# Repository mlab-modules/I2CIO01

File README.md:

# I2CIO01A - I2C IO Expander

## Overview

The I2CIO01 module is a GPIO expander designed for operation in the range of 1.65 to 5.5 V. It provides general-purpose remote I/O expansion via the I²C interface. The module comprises two 8-bit Configurable, Input Ports, Output Port, and Polarity Inversion registers.

## Features

- **Operating Voltage:** 1.65 to 5.5 V
- **Interfaces:** I²C, up to 400 kHz
- **GPIO Ports:** 16-bit expansion using either TCA6416A or TCA9535 IC
- **Address Selection:**
  - TCA6416A: 2 I2C addresses, includes a reset pin
  - TCA9535: 4 I2C addresses
- **Interrupt Capabilities:** Both ICs support interrupt output
- **Package Dimensions:** 40.13 x 40.13 x 16 mm

## Technical Specifications

| Parameter        | Value        | Note                                |
|------------------|--------------|-------------------------------------|
| Power Supply     | Max. 3.6 V   |                                     |
| ICs Used         | TCA6416A or TCA9535 |                              |
| Interface bus        | I²C          | Frequency up to 400 kHz             |
| Main Usage       | I²C IO expander |                                     |
| Dimensions       | 40.13 x 40.13 x 16 mm | Height above the baseboard   |

## Design Details

### IC Selection variants
- **TCA6416A:**
  - Populate RES, do not populate ADR X
  - Jumper to Vccp and VDD
- **TCA9535:**
  - Do not populate RES, populate ADR X
  - Jumper to Vccp and VDD

### Schematic and Layout

The module's design and layout files can be found in the `hw/sch_pcb` directory. The board is designed using KiCad.

## Bill of Materials

| Designator      | Type                    | Package                    | Quantity |
|-----------------|-------------------------|----------------------------|----------|
| J3              | JUMP_3X2                | Pin_Header_Straight_2x03   | 1        |
| R1, R2, R3, ... | 10k                     | SMD-0805                   | 13       |
| U1              | TCA6416A                | TSSOP-28                   | 1        |
| J8, J5          | CONN1_2                 | Pin_Header_Straight_1x02   | 2        |
| P1, P2, P3, P4  | MountingHole_3mm        |                            | 4        |
| J1              | JUMP_2X2                | Pin_Header_Straight_2x02   | 1        |
| J2              | JUMP_5X2                | Pin_Header_Straight_2x05   | 1        |
| J6, J7          | JUMP_8X2                | Pin_Header_Straight_2x08   | 2        |
| J4, J9          | CONN_2                  | Pin_Header_Straight_1x02   | 2        |
| C1              | 10uF                    | SMD-0805                   | 1        |
| C2              | 100nF                   | SMD-0805                   | 1        |
| D1              | BZV55C-3,6V             | Diode-MiniMELF_Standard    | 1        |

## Assembly and Testing

1. **Assembly:** Follow the provided schematic and BOM for assembling the module.
2. **Initial Inspection:** Perform a visual inspection to ensure no shorts on the power supply.
3. **Testing:** No additional setup is required beyond the initial inspection.

For more detailed information on each component, please refer to their respective datasheets:

- [TCA6416A Datasheet](https://www.ti.com/product/TCA6416A)
- [TCA9535 Datasheet](https://www.ti.com/product/TCA9535)

## Contributing

Contributions are welcome! Please fork this repository and submit a pull request with your changes.

## Contact

For more information, visit the [MLAB website](http://www.mlab.cz) or contact us at support@mlab.cz.

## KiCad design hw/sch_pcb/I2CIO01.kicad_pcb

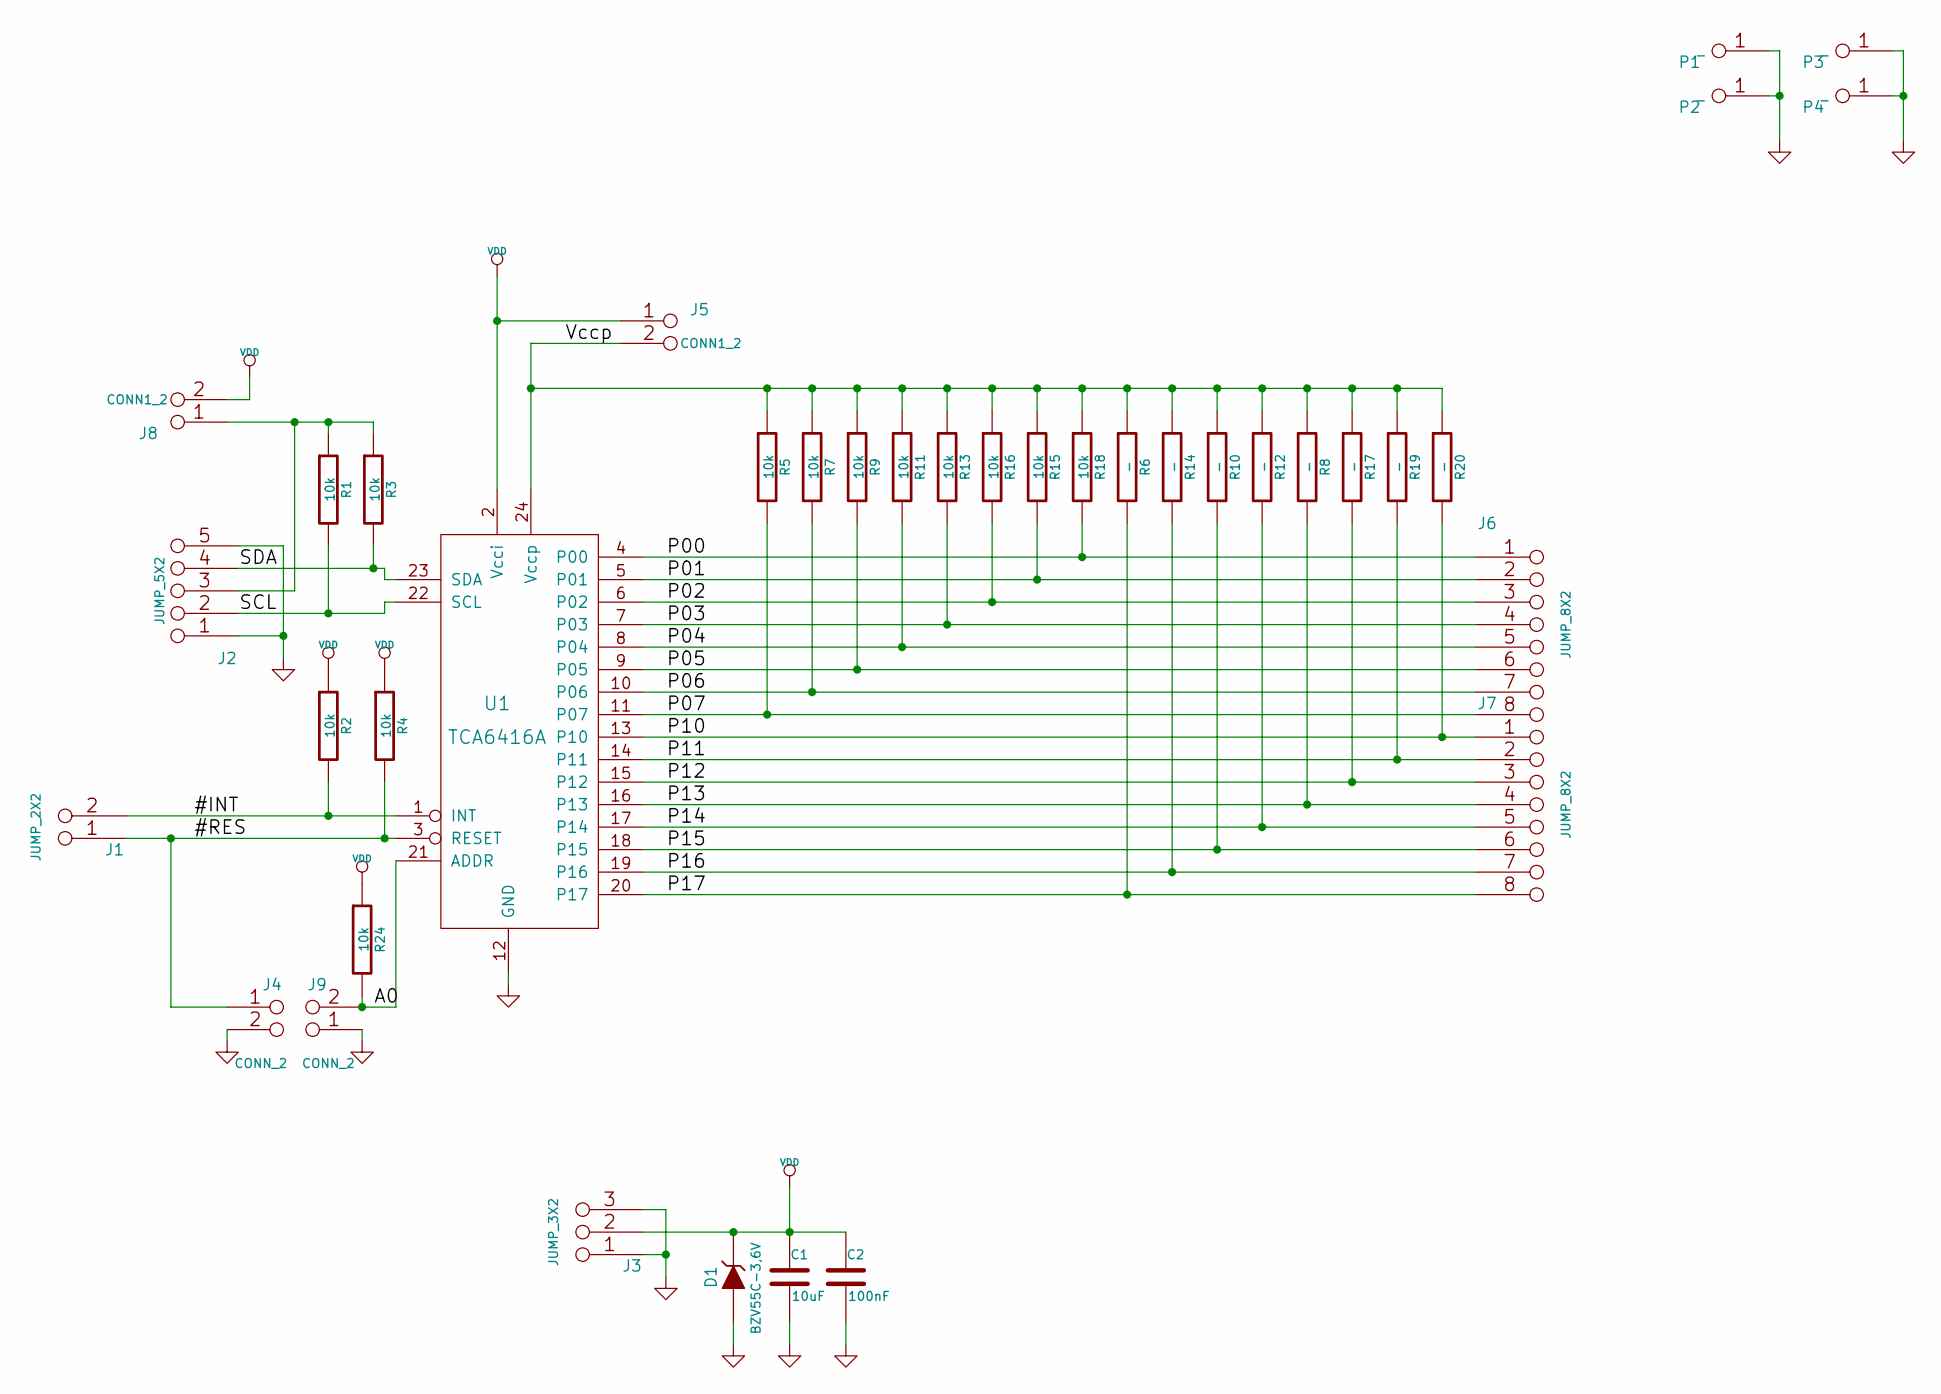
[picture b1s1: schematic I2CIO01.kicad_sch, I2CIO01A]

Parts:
C1: 10uF; SMD-0805
C2: 100nF; SMD-0805
D1: BZV55C-3,6V; Diode-MiniMELF_Standard
J1: JUMP_2X2; Pin_Header_Straight_2x02
J2: JUMP_5X2; Pin_Header_Straight_2x05
J3: JUMP_3X2; Pin_Header_Straight_2x03
J4, J9: CONN_2; Pin_Header_Straight_1x02
J5, J8: CONN1_2; Pin_Header_Straight_1x02
J6, J7: JUMP_8X2; Pin_Header_Straight_2x08
P1, P2, P3, P4: _; MountingHole_3mm
R1, R2, R3, R4, R5, R7, R9, R11, R13, R15, R16, R18, R24: 10k; SMD-0805
R6, R8, R10, R12, R14, R17, R19, R20: -; SMD-0805
U1: TCA6416A; TSSOP-28

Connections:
/#INT: J1.2 (1), J1.3, R2.2, U1.1 (INT)
/#RES: J1.1, J1.4, J4.1, R4.2, U1.3 (RESET)
/A0: J9.2 (PM), R24.2, U1.21 (ADDR)
/P00: J6.1, J6.16, R18.2, U1.4 (P00)
/P01: J6.2, J6.15, R15.2, U1.5 (P01)
/P02: J6.3, J6.14, R16.2, U1.6 (P02)
/P03: J6.4, J6.13, R13.2, U1.7 (P03)
/P04: J6.5, J6.12, R11.2, U1.8 (P04)
/P05: J6.6, J6.11, R9.2, U1.9 (P05)
/P06: J6.7, J6.10, R7.2, U1.10 (P06)
/P07: J6.8, J6.9, R5.2, U1.11 (P07)
/P10: J7.1, J7.16, R20.2, U1.13 (P10)
/P11: J7.2, J7.15, R19.2, U1.14 (P11)
/P12: J7.3, J7.14, R17.2, U1.15 (P12)
/P13: J7.4, J7.13, R8.2, U1.16 (P13)
/P14: J7.5, J7.12, R12.2, U1.17 (P14)
/P15: J7.6, J7.11, R10.2, U1.18 (P15)
/P16: J7.7, J7.10, R14.2, U1.19 (P16)
/P17: J7.8, J7.9, R6.2, U1.20 (P17)
/SCL: J2.2, J2.9, R1.2, U1.22 (SCL)
/SDA: J2.4, J2.7, R3.2, U1.23 (SDA)
/Vccp: J5.2 (PM), R5.1, R6.1, R7.1, R8.1, R9.1, R10.1, R11.1, R12.1, R13.1, R14.1, R15.1, R16.1, R17.1, R18.1, R19.1, R20.1, U1.24 (Vccp)
GND: C1.2, C2.2, D1.1 (A), J2.1, J2.5, J2.6, J2.10, J3.1, J3.3, J3.4, J3.6, J4.2 (PM), J9.1, P1.1, P2.1, P3.1, P4.1, U1.12 (GND)
unnamed: J2.3, J2.8, J8.1, R1.1, R3.1
VDD: C1.1, C2.1, D1.2 (K), J3.2 (1), J3.5, J5.1, J8.2 (PM), R2.1, R4.1, R24.1, U1.2 (Vcci)

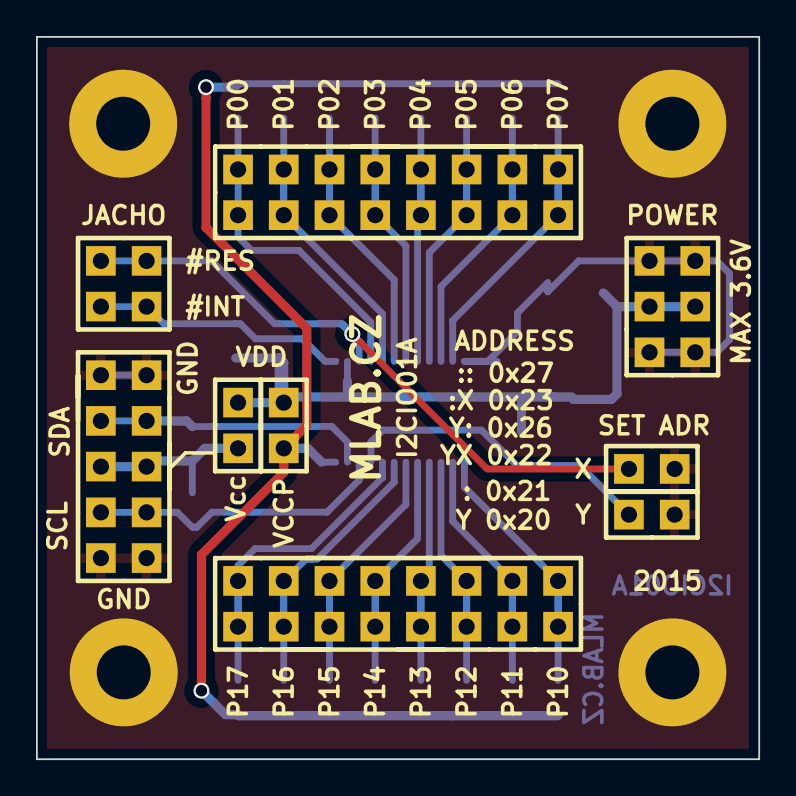
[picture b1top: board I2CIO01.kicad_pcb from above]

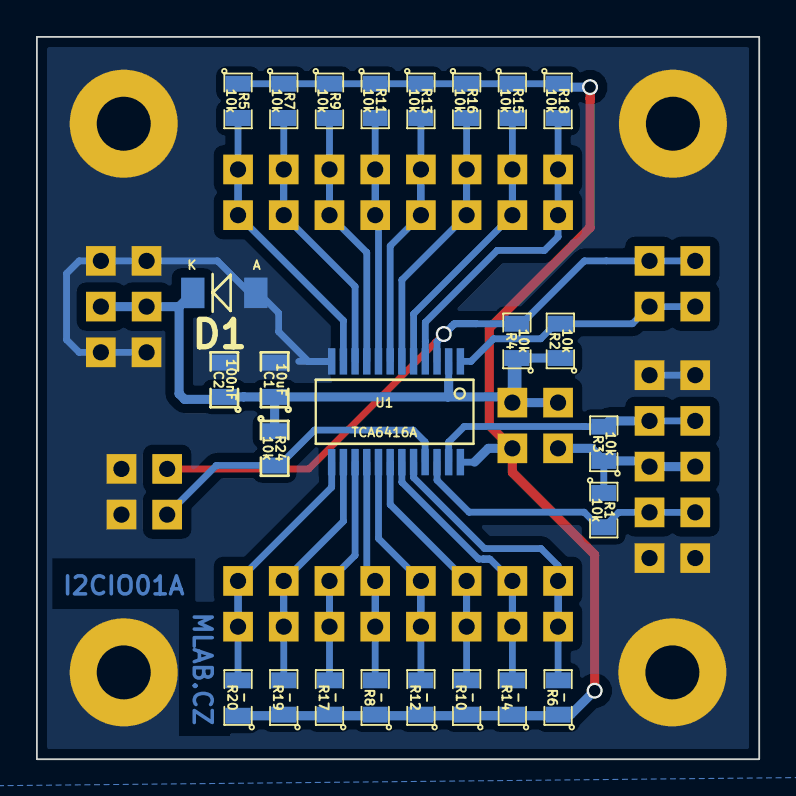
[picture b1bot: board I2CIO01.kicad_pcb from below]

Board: 2 copper layers, 40.1 x 40.1 mm, 38 parts (25 on the bottom side), 25 nets.

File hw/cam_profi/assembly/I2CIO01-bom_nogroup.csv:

Component,Description,Part,References,Value,Footprint,Quantity Per PCB,Datasheet
1,,C,C2,100nF,SMD-0805,1,
2,,C,C1,10uF,SMD-0805,1,
3,,ZENER,D1,"BZV55C-3,6V",Diode-MiniMELF_Standard,1,
4,,CONN1_2,J5J8,CONN1_2,Pin_Header_Straight_1x02,2,
5,,CONN_2,J4J9,CONN_2,Pin_Header_Straight_1x02,2,
6,,JUMP_2X2,J1,JUMP_2X2,Pin_Header_Straight_2x02,1,
7,,JUMP_3X2,J3,JUMP_3X2,Pin_Header_Straight_2x03,1,
8,,JUMP_5X2,J2,JUMP_5X2,Pin_Header_Straight_2x05,1,
9,,JUMP_8X2,J6J7,JUMP_8X2,Pin_Header_Straight_2x08,2,
10,,R,R1R2R3R4R5R7R9R11R13R15R16R18R24,10k,SMD-0805,13,
11,,R,R6R8R10R12R14R17R19R20,-,SMD-0805,8,
12,,TCA6416A,U1,TCA6416A,TSSOP-28,1,

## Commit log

2017-08-22 rename category folders
2017-08-22 rename files and module folders
2017-08-22 change images path
2017-08-22 create hw folder
2017-08-22 change filepaths
2017-08-22 rm empty json html files, rename module.json files
2017-08-22 new .json files
2017-11-06 [MLABweb] 2017-11-06 09:59:10 I2CIO01A
2018-02-25 Přesun špatně zařazených modulů + oprava v DB MLABwebu.
2018-11-05 Presun obrazku do slozky img. Pregenerovani dokumentaci.
2022-04-06 Update actions products
2022-04-06 automated commit; add github actions
2023-05-25 Update metadata files
2023-05-28 Update workflow files
2023-07-05 automated commit; rename source files to new naming convence
2023-09-16 Update image to image_title
2023-09-16 Update status
2024-07-07 Update documentation and upgrade to KiCADv7.
2024-07-07 Update PCB to KiCADv7.
